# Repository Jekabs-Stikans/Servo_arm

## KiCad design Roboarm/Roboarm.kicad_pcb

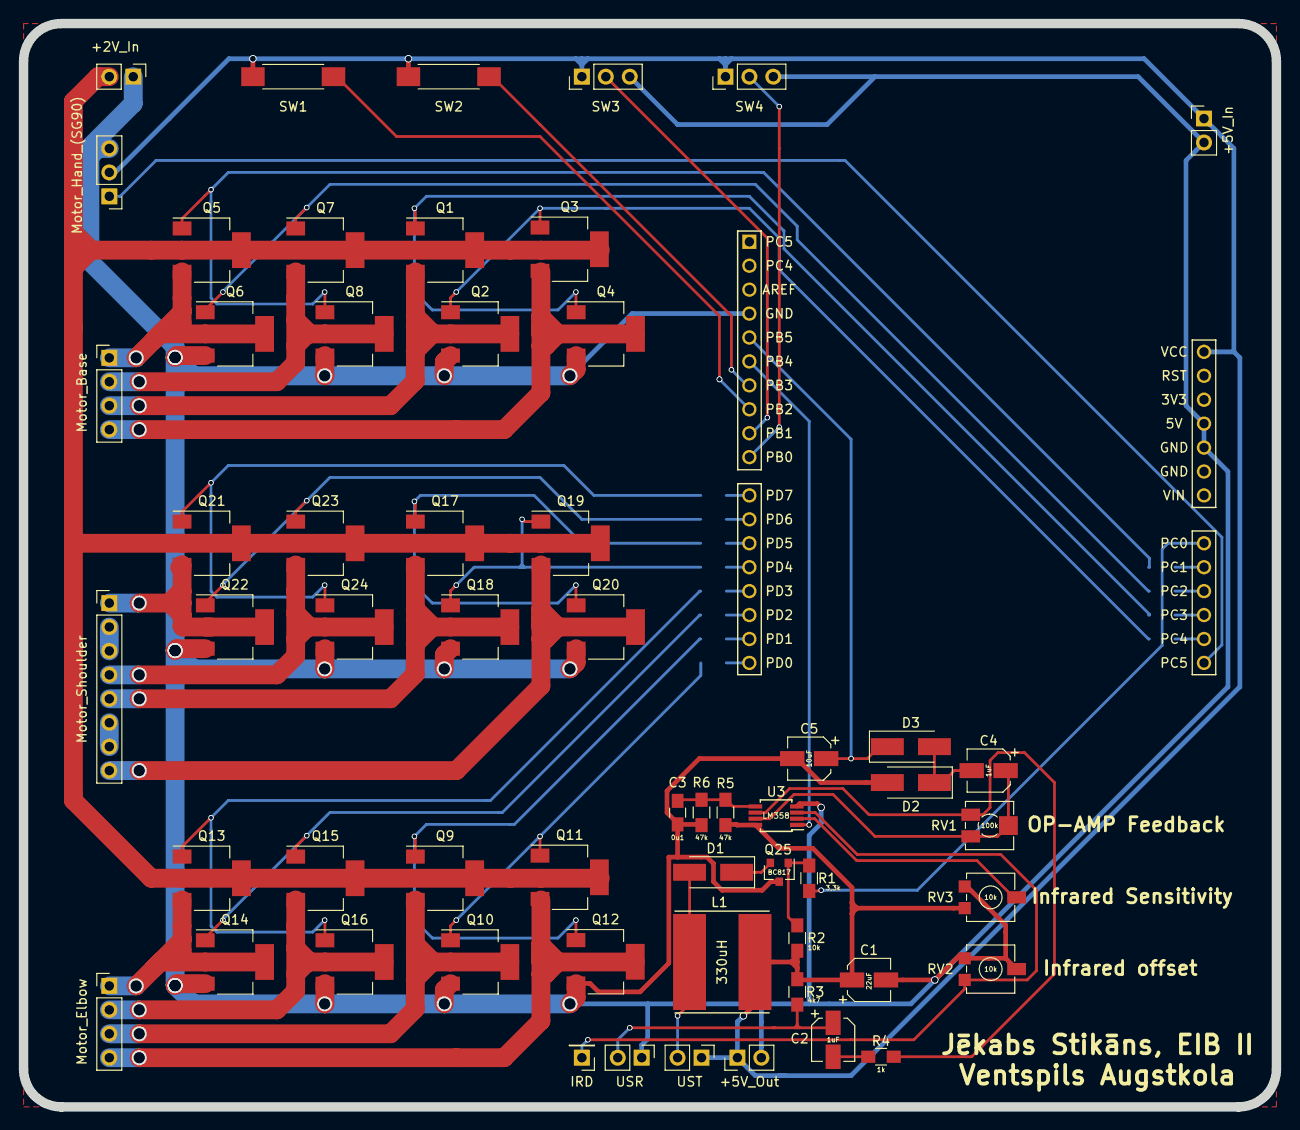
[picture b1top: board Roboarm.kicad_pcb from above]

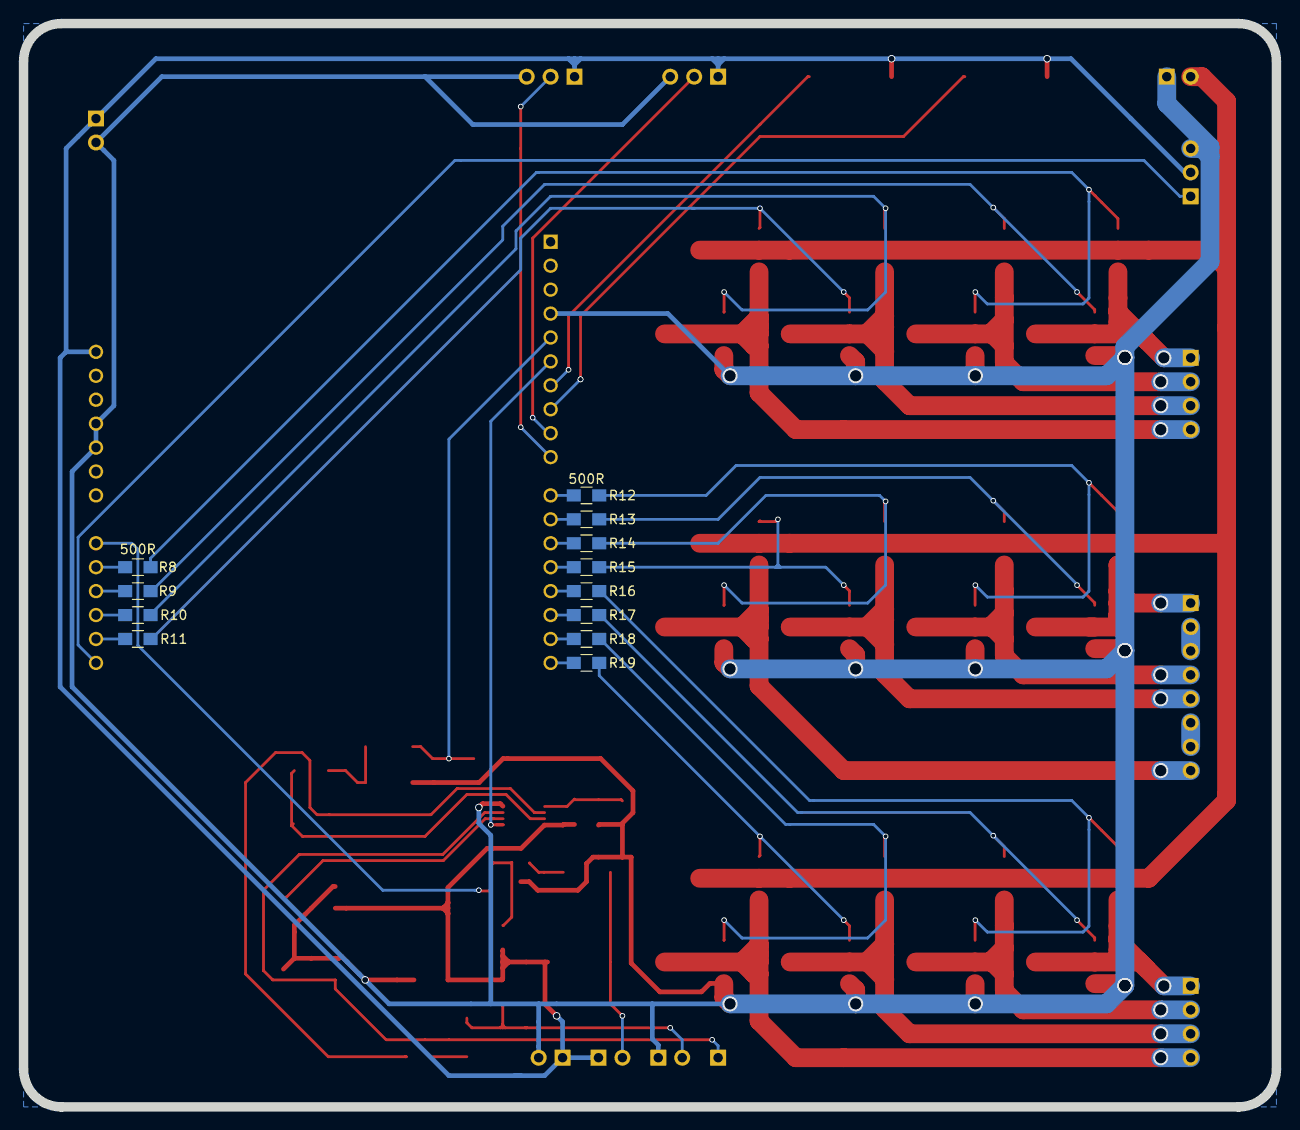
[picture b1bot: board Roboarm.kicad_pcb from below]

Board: 2 copper layers, 133.0 x 115.0 mm, 71 parts (12 on the bottom side), 60 nets.

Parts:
C1: 22uF; CP_Elec_4x5.3
C2, C4: 1uF; CP_Elec_4x5.3
C3: 0u1; C_0805_HandSoldering
C5: 10uF; CP_Elec_4x5.3
D1, D2, D3: D_ALT; D_SMA_Handsoldering
J1: +5V_Out; Pin_Header_Straight_1x02_Pitch2.54mm
J2: +2V_In; Pin_Header_Straight_1x02_Pitch2.54mm
J3: +5V_In; Pin_Header_Straight_1x02_Pitch2.54mm
J7: IRD; Pin_Header_Straight_1x01_Pitch2.54mm
L1: 330uH; Inductor_Taiyo-Yuden_NR-80xx_HandSoldering
LS1: UST; Pin_Header_Straight_1x02_Pitch2.54mm
M1: Motor_Base; Pin_Header_Straight_1x04_Pitch2.54mm
M2: Motor_Shoulder; Pin_Header_Straight_1x08_Pitch2.54mm
M3: Motor_Elbow; Pin_Header_Straight_1x04_Pitch2.54mm
M4: Motor_Hand_(SG90); Pin_Header_Straight_1x03_Pitch2.54mm
MC1: USR; Pin_Header_Straight_1x02_Pitch2.54mm
MCU1: ATmega328P; ATmega328P_Xplained_mini
Q1, Q2, Q3, Q4, Q5, Q6, Q7, Q8, Q9, Q10, Q11, Q12, Q13, Q14, Q15, Q16, Q17, Q18, Q19, Q20, Q21, Q22, Q23, Q24: FZT651; SOT-223
Q25: BC817; SOT-23
R1: 3,3k; R_0805_HandSoldering
R2: 10k; R_0805_HandSoldering
R3: 4k7; R_0805_HandSoldering
R4: 1k; R_0805_HandSoldering
R5, R6: 47k; R_0805_HandSoldering
R8, R9, R10, R11, R12, R13, R14, R15, R16, R17, R18, R19: 500R; R_0805_HandSoldering
RV1: 100k; Potentiometer_Trimmer_Vishay_TS53YJ
RV2, RV3: 10k; Potentiometer_Trimmer_Vishay_TS53YL
SW1, SW2: SW_Push; SW_SPST_REED_CT05-XXXX-G1
SW3, SW4: Switch_Custom; PinHeader_1x03_P2.54mm_Vertical
U3: LM358; MSOP-8_3x3mm_Pitch0.65mm

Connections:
+5V: C1.1, J1.1, J3.1, L1.2, LS1.1, M4.2, MCU1.20, R2.1, R3.1, R5.1, RV3.1, SW1.1, SW2.1, SW3.1, SW4.1, U3.8
/+2V: J2.2, Q1.2, Q1.4, Q3.2, Q3.4, Q5.2, Q5.4, Q7.2, Q7.4, Q9.2, Q9.4, Q11.2, Q11.4, Q13.2, Q13.4, Q15.2, Q15.4, Q17.2, Q17.4, Q19.2, Q19.4, Q21.2, Q21.4, Q23.2, Q23.4
/Collision_detector/Interrupt: MCU1.6, U3.1
/StepMotorBase/A: Q5.1, Q8.1, R8.1
/StepMotorBase/B: Q6.1, Q7.1, R9.1
/StepMotorBase/C: Q1.1, Q4.1, R10.1
/StepMotorBase/D: Q2.1, Q3.1, R11.1
/StepMotorElbow/A: Q13.1, Q16.1, R16.1
/StepMotorElbow/B: Q14.1, Q15.1, R17.1
/StepMotorElbow/C: Q9.1, Q12.1, R18.1
/StepMotorElbow/D: Q10.1, Q11.1, R19.1
/StepMotorShoulder/A: Q21.1, Q24.1, R12.1
/StepMotorShoulder/B: Q22.1, Q23.1, R13.1
/StepMotorShoulder/C: Q17.1, Q20.1, R14.1
/StepMotorShoulder/D: Q18.1, Q19.1, R15.1
/Ultrasonic_distancer/Ultrasonic_Out: C5.1, D3.1, MCU1.5
/Ultrasonic_distancer/Ultrasonic_PWM: MCU1.27, R1.1
GND: C1.2, C3.2, C5.2, D2.2, J1.2, J2.1, J3.2, M4.3, MC1.1, MCU1.4, MCU1.23, MCU1.24, Q2.3, Q4.3, Q6.3, Q8.3, Q10.3, Q12.3, Q14.3, Q16.3, Q18.3, Q20.3, Q22.3, Q24.3, Q25.3, R6.2, RV2.2, RV2.3, RV3.3, SW3.3, SW4.3, U3.4
unnamed: C2.1, MC1.2, R3.2
unnamed: C2.2, R4.1
unnamed: C3.1, R5.2, R6.1, U3.5
unnamed: C4.1, RV1.1, RV1.2, U3.7
unnamed: C4.2, D2.1, D3.2
unnamed: D1.1, Q25.2
unnamed: D1.2, L1.1, LS1.2
unnamed: J7.1, RV2.1, U3.3
unnamed: M1.1, Q5.3, Q6.2, Q6.4
unnamed: M1.2, Q7.3, Q8.2, Q8.4
unnamed: M1.3, Q1.3, Q2.2, Q2.4
unnamed: M1.4, Q3.3, Q4.2, Q4.4
unnamed: M2.1, Q21.3, Q22.2, Q22.4
unnamed: M2.2, M2.3
unnamed: M2.4, Q23.3, Q24.2, Q24.4
unnamed: M2.5, Q17.3, Q18.2, Q18.4
unnamed: M2.6, M2.7
unnamed: M2.8, Q19.3, Q20.2, Q20.4
unnamed: M3.1, Q13.3, Q14.2, Q14.4
unnamed: M3.2, Q15.3, Q16.2, Q16.4
unnamed: M3.3, Q9.3, Q10.2, Q10.4
unnamed: M3.4, Q11.3, Q12.2, Q12.4
unnamed: M4.1, MCU1.32
unnamed: MCU1.7, SW2.2
unnamed: MCU1.8, SW1.2
unnamed: MCU1.9, SW3.2
unnamed: MCU1.10, SW4.2
unnamed: MCU1.11, R12.2
unnamed: MCU1.12, R13.2
unnamed: MCU1.13, R14.2
unnamed: MCU1.14, R15.2
unnamed: MCU1.15, R16.2
unnamed: MCU1.16, R17.2
unnamed: MCU1.17, R18.2
unnamed: MCU1.18, R19.2
unnamed: MCU1.28, R8.2
unnamed: MCU1.29, R9.2
unnamed: MCU1.30, R10.2
unnamed: MCU1.31, R11.2
unnamed: Q25.1, R1.2, R2.2
unnamed: R4.2, RV1.3, U3.6
unnamed: RV3.2, U3.2

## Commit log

2021-03-26 Kursa darba projekta augšupielāde
